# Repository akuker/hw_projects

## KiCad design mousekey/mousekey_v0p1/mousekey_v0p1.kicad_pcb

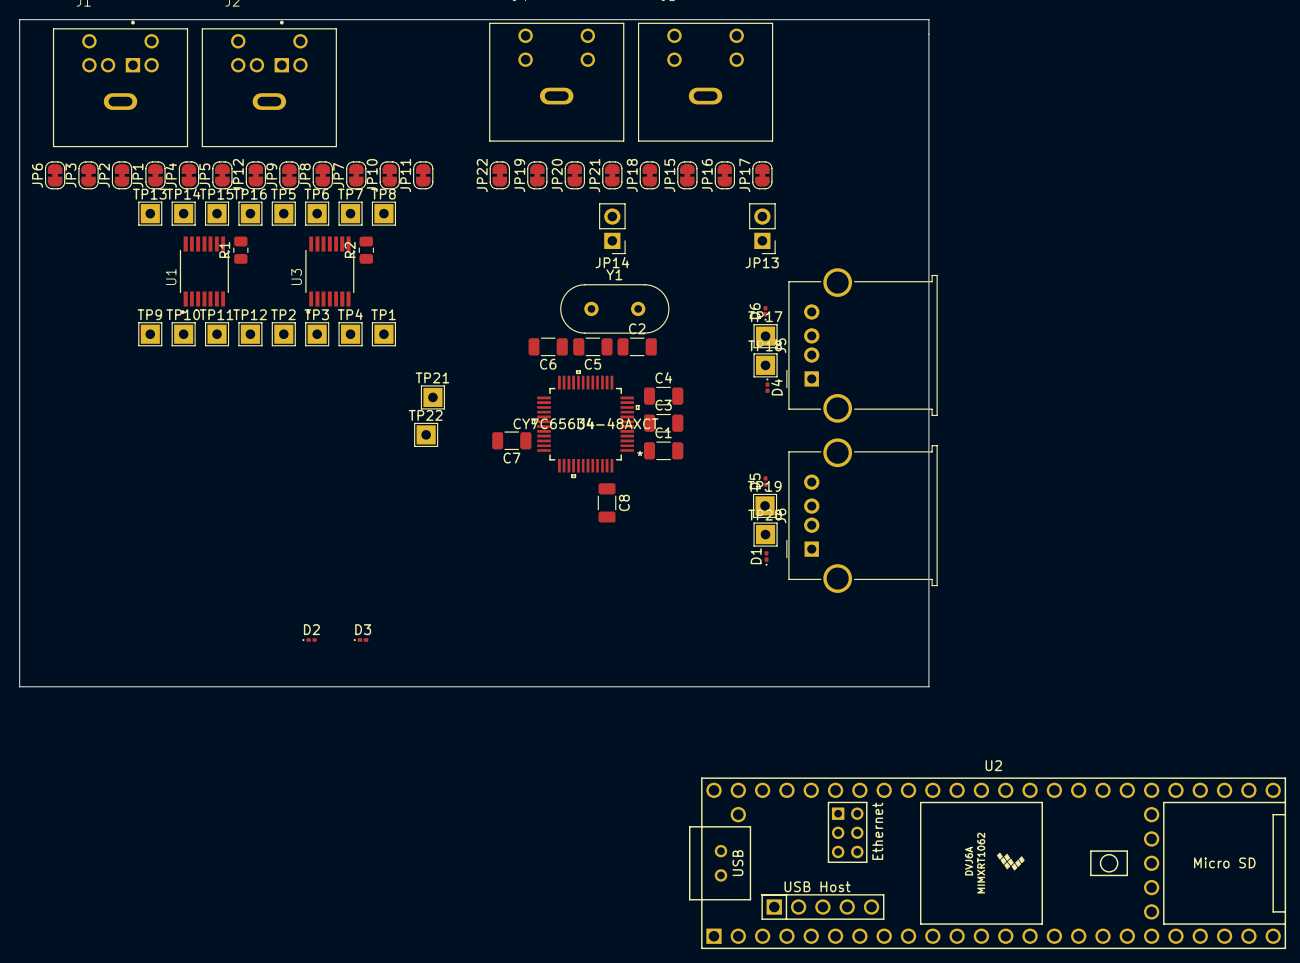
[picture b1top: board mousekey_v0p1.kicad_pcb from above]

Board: 2 copper layers, 95.0 x 69.7 mm, 71 parts (0 on the bottom side), 54 nets, no tracks yet.

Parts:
C1, C3, C4, C6, C7, C8: 0.1u; C_1206_3216Metric
C2, C5: 20p; C_1206_3216Metric
D1, D2, D3, D4, D5, D6: PGB1010603MR; D_0201_0603Metric
J1, J2: MD-60S; CUI_MD-60S
J3, J4: MD-40S; CUI_MD-40S
J5, J6: USB_A; USB_A_Molex_67643_Horizontal
JP1, JP2, JP3, JP4, JP5, JP6, JP7, JP8, JP9, JP10, JP11, JP12, JP15, JP16, JP17, JP18, JP19, JP20, JP21, JP22: SolderJumper_2_Bridged; SolderJumper-2_P1.3mm_Bridged_RoundedPad1.0x1.5mm
JP13, JP14: Jumper_2_Bridged; PinHeader_1x02_P2.54mm_Vertical
R1, R2: 0 ohm; R_0805_2012Metric
TP1, TP2, TP3, TP4, TP5, TP6, TP7, TP8, TP9, TP10, TP11, TP12, TP13, TP14, TP15, TP16, TP17, TP18, TP19, TP20, TP21, TP22: TestPoint; TestPoint_THTPad_2.0x2.0mm_Drill1.0mm
U1, U3: LSF0204DPWR; SOP65P640X120-14N
U2: Teensy4.1; Teensy41
U4: CY7C65634-48AXCT
Y1: 12MHz; Crystal_HC49-U_Vertical

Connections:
+3V3: U1.1 (VREF_A), U3.1 (VREF_A)
+5V: C8.1, J5.1 (VBUS), J6.1 (VBUS), JP3.1 (A), JP13.1 (A), JP14.1 (A), U1.14 (VREF_B), U3.14 (VREF_B), U4.47 (VCC)
ADB_A_Data: JP15.1 (A), TP5.1, U3.13 (B1)
ADB_A_PWR: JP16.1 (A), TP6.1, U3.12 (B2)
ADB_B_Data: JP19.1 (A), TP7.1, U3.11 (B3)
ADB_B_PWR: JP20.1 (A), TP8.1, U3.10 (B4)
GND: C1.2, C2.2, C3.2, C4.2, C5.2, C7.2, C8.2, J1.S1 (SHIELD), J2.S1 (SHIELD), J3.S1 (SHIELD), J4.S1 (SHIELD), J5.4 (GND), J6.4 (GND), JP4.1 (A), JP10.1 (A), JP18.1 (A), JP22.1 (A), R1.1, R2.1, U1.7 (GND), U3.7 (GND), U4.2 (GND), U4.8 (GND), U4.13 (GND), U4.20 (GND)
GNDPWR: D1.2 (A2), D2.2 (A2), D3.2 (A2), D4.2 (A2), D5.2 (A2), D6.2 (A2), J5.5 (Shield), J6.5 (Shield)
unnamed: J1.1, JP1.2 (B)
unnamed: J1.2, JP2.2 (B)
unnamed: J1.3, JP3.2 (B)
unnamed: J1.5, JP4.2 (B)
unnamed: J1.6, JP5.2 (B)
unnamed: J1.8, JP6.2 (B)
unnamed: J2.1, JP7.2 (B)
unnamed: J2.2, JP8.2 (B)
unnamed: J2.3, JP9.2 (B)
unnamed: J2.5, JP10.2 (B)
unnamed: J2.6, JP11.2 (B)
unnamed: J2.8, JP12.2 (B)
unnamed: J3.3, JP15.2 (B)
unnamed: J3.5, JP16.2 (B)
unnamed: J3.6, JP17.2 (B)
unnamed: J3.8, JP18.2 (B)
unnamed: J4.3, JP19.2 (B)
unnamed: J4.5, JP20.2 (B)
unnamed: J4.6, JP21.2 (B)
unnamed: J4.8, JP22.2 (B)
unnamed: JP13.2 (B), JP17.1 (A)
unnamed: JP14.2 (B), JP21.1 (A)
unnamed: R1.2, U1.8 (~EN)
unnamed: R2.2, U3.8 (~EN)
PS2_A_CLK: JP5.1 (A), TP14.1, U1.12 (B2)
PS2_A_Data: JP1.1 (A), TP13.1, U1.13 (B1)
PS2_B_CLK: JP11.1 (A), TP16.1, U1.10 (B4)
PS2_B_Data: JP7.1 (A), TP15.1, U1.11 (B3)
TTL_ADB_A_Data: TP1.1, U3.2 (A1)
TTL_ADB_A_PWR: TP2.1, U3.3 (A2)
TTL_ADB_B_Data: TP3.1, U3.4 (A3)
TTL_ADB_B_PWR: TP4.1, U3.5 (A4)
TTL_PS2_A_CLK: TP10.1, U1.3 (A2)
TTL_PS2_A_Data: TP9.1, U1.2 (A1)
TTL_PS2_B_CLK: TP12.1, U1.5 (A4)
TTL_PS2_B_Data: TP11.1, U1.4 (A3)
USB_DD1_N: D1.1 (A1), J6.2 (D-), TP20.1, U4.5 (DD-1)
USB_DD1_P: D5.1 (A1), J6.3 (D+), TP19.1, U4.6 (DD+1)
USB_DD2_N: D4.1 (A1), J5.2 (D-), TP18.1, U4.9 (DD-2)
USB_DD2_P: D6.1 (A1), J5.3 (D+), TP17.1, U4.10 (DD+2)
USB_DIN_N: D3.1 (A1), TP22.1, U4.3 (D-)
USB_DIN_P: D2.1 (A1), TP21.1, U4.4 (D+)
USB_VCC_A: C1.1, C3.1, C4.1, C6.1, U4.1 (VCC_A), U4.7 (VCC_A), U4.12 (VCC_A), U4.16 (VCC_A)
USB_VCC_D: C7.1, U4.34 (VCC_D)
USB_XIN: C2.1, U4.14 (XIN), Y1.1
USB_XOUT: C5.1, U4.15 (XOUT), Y1.2

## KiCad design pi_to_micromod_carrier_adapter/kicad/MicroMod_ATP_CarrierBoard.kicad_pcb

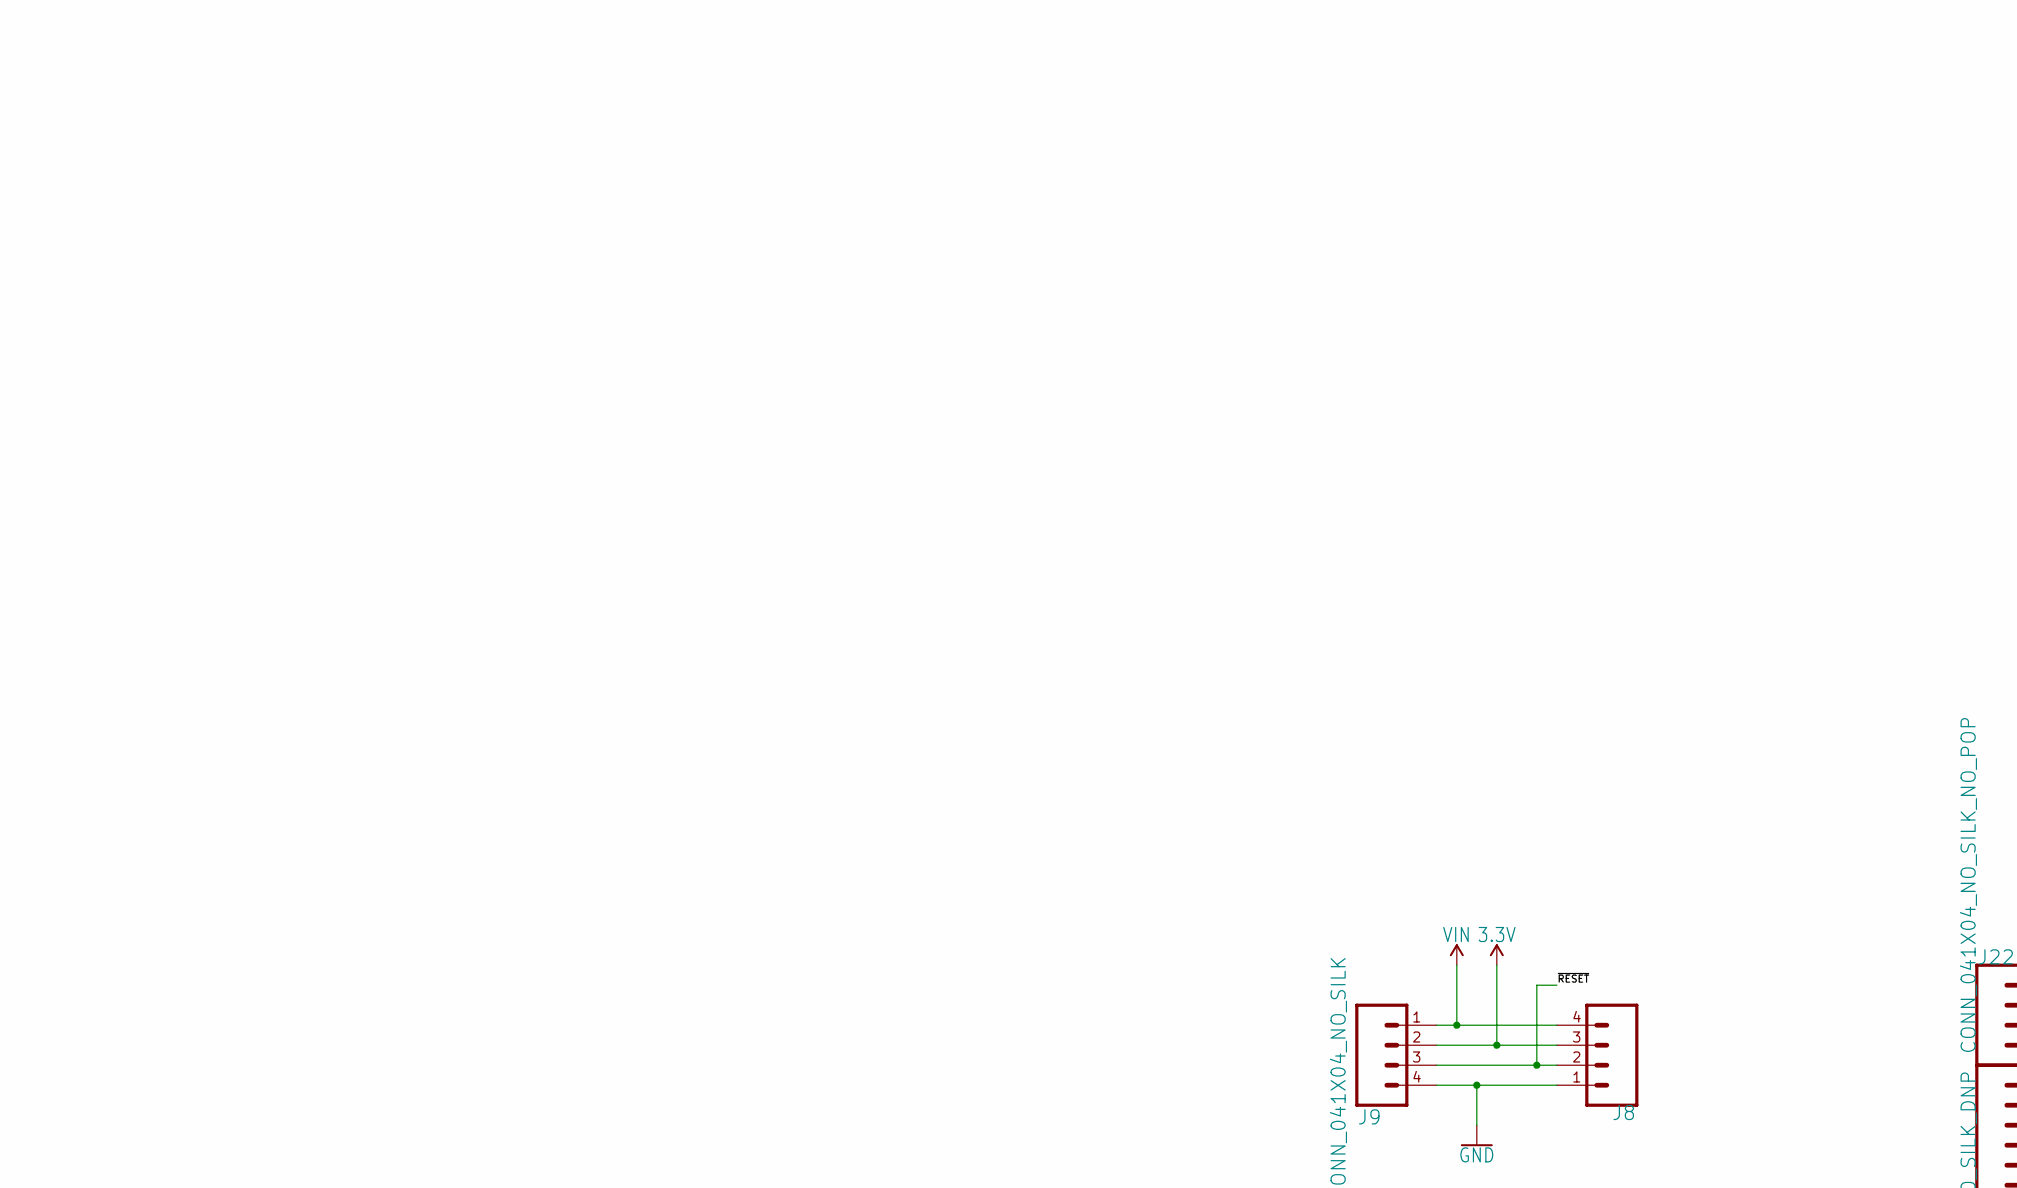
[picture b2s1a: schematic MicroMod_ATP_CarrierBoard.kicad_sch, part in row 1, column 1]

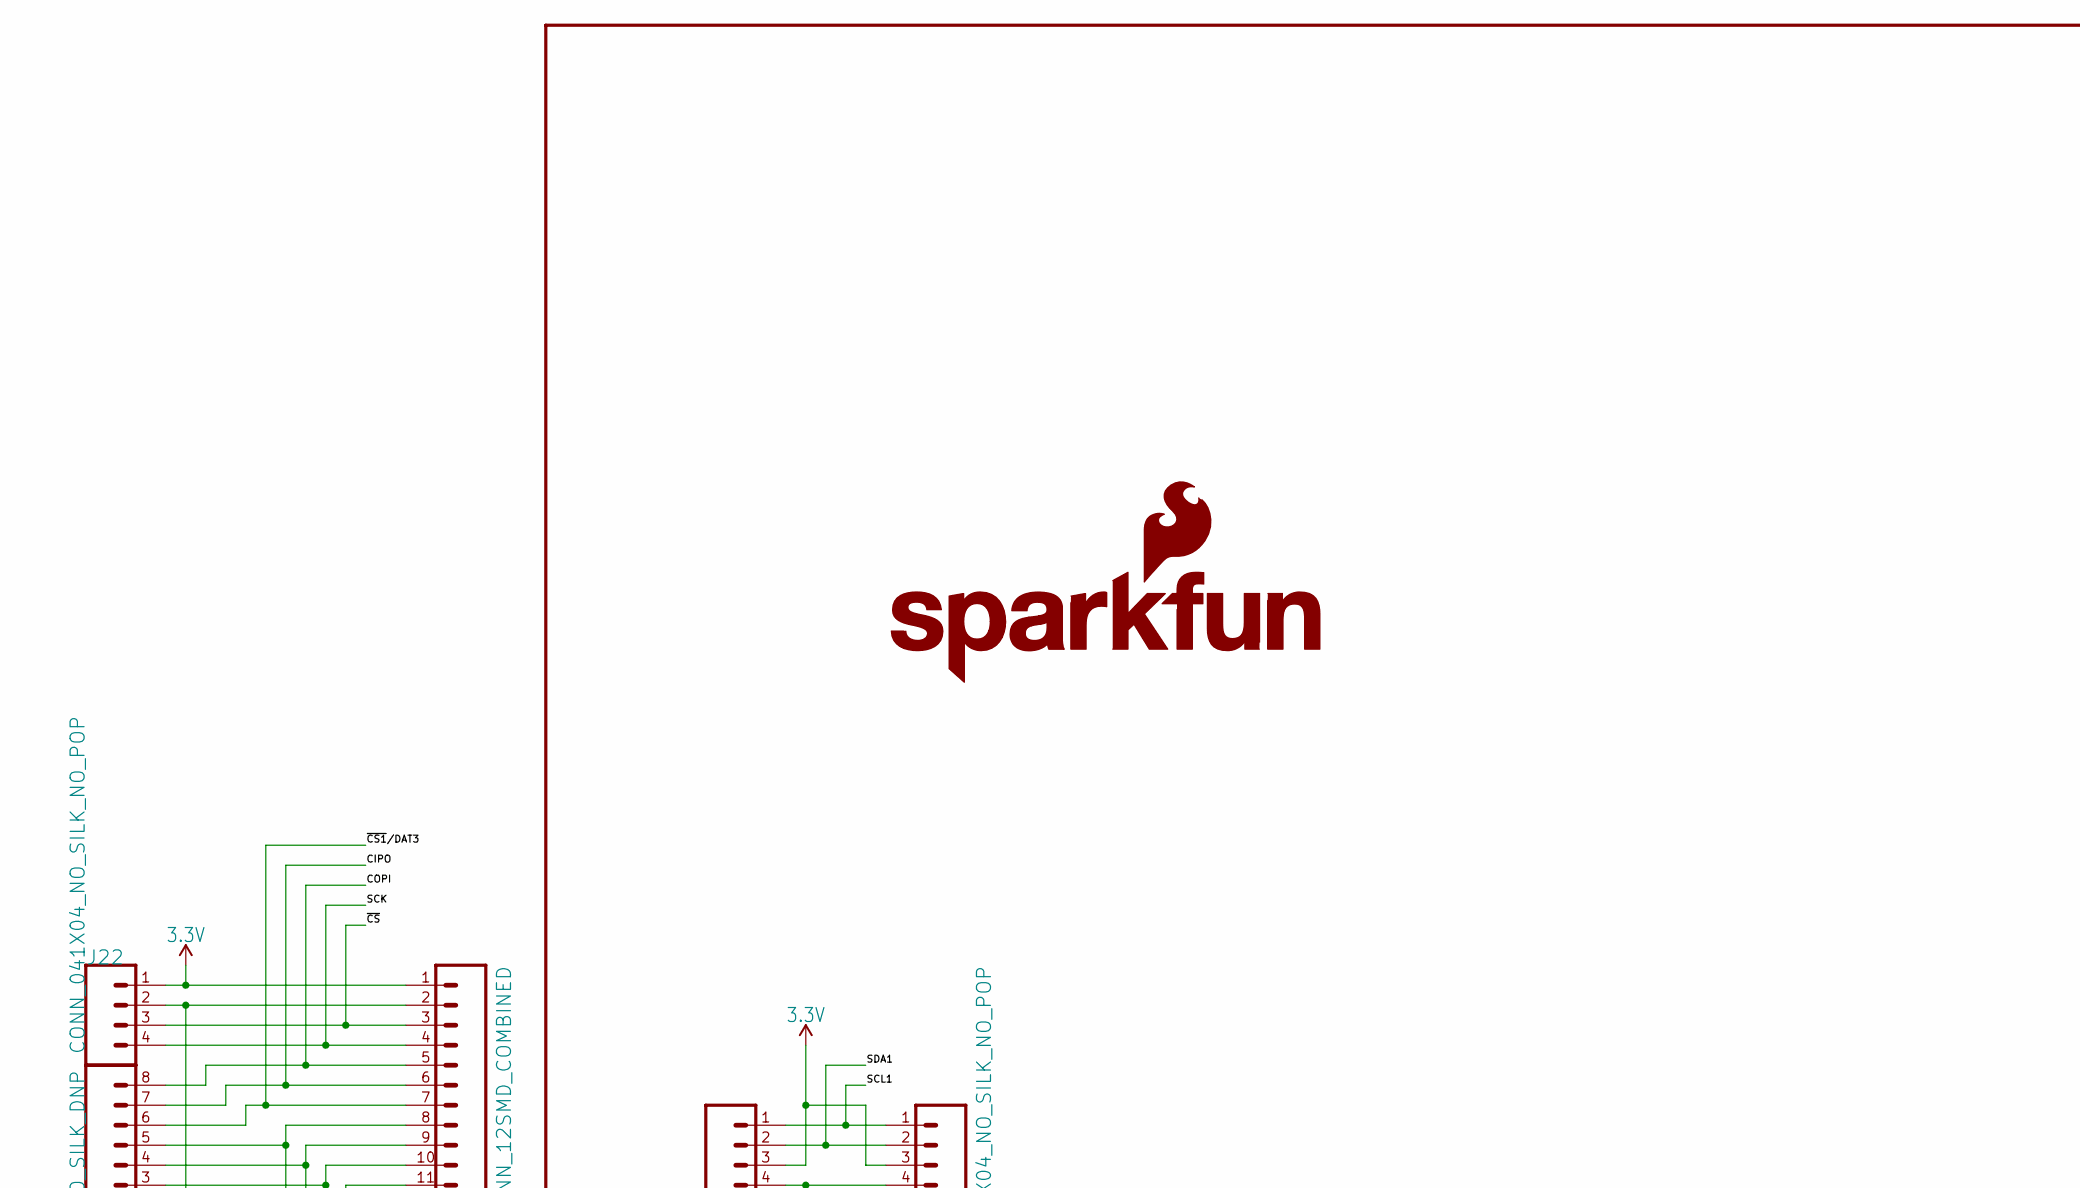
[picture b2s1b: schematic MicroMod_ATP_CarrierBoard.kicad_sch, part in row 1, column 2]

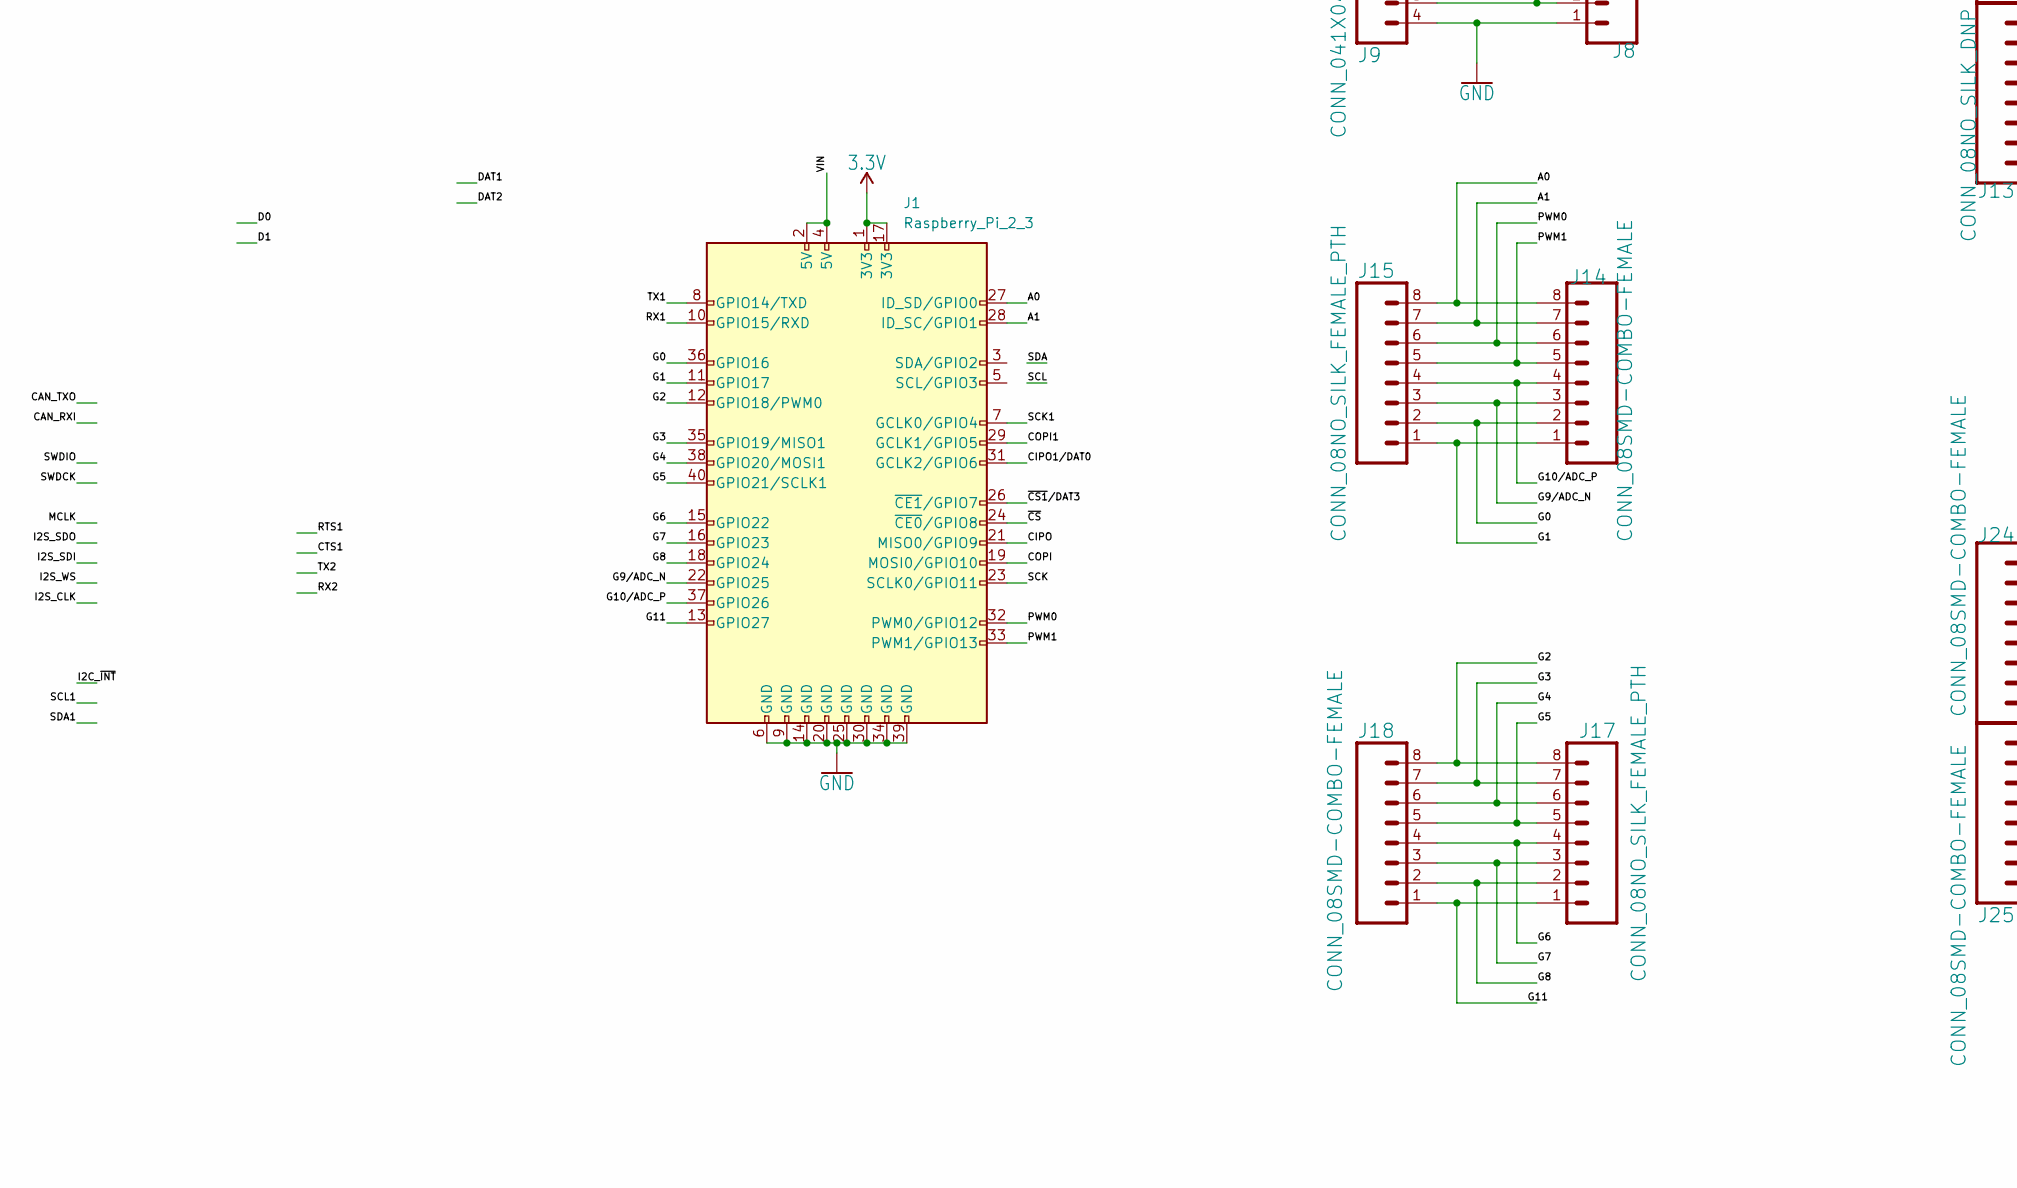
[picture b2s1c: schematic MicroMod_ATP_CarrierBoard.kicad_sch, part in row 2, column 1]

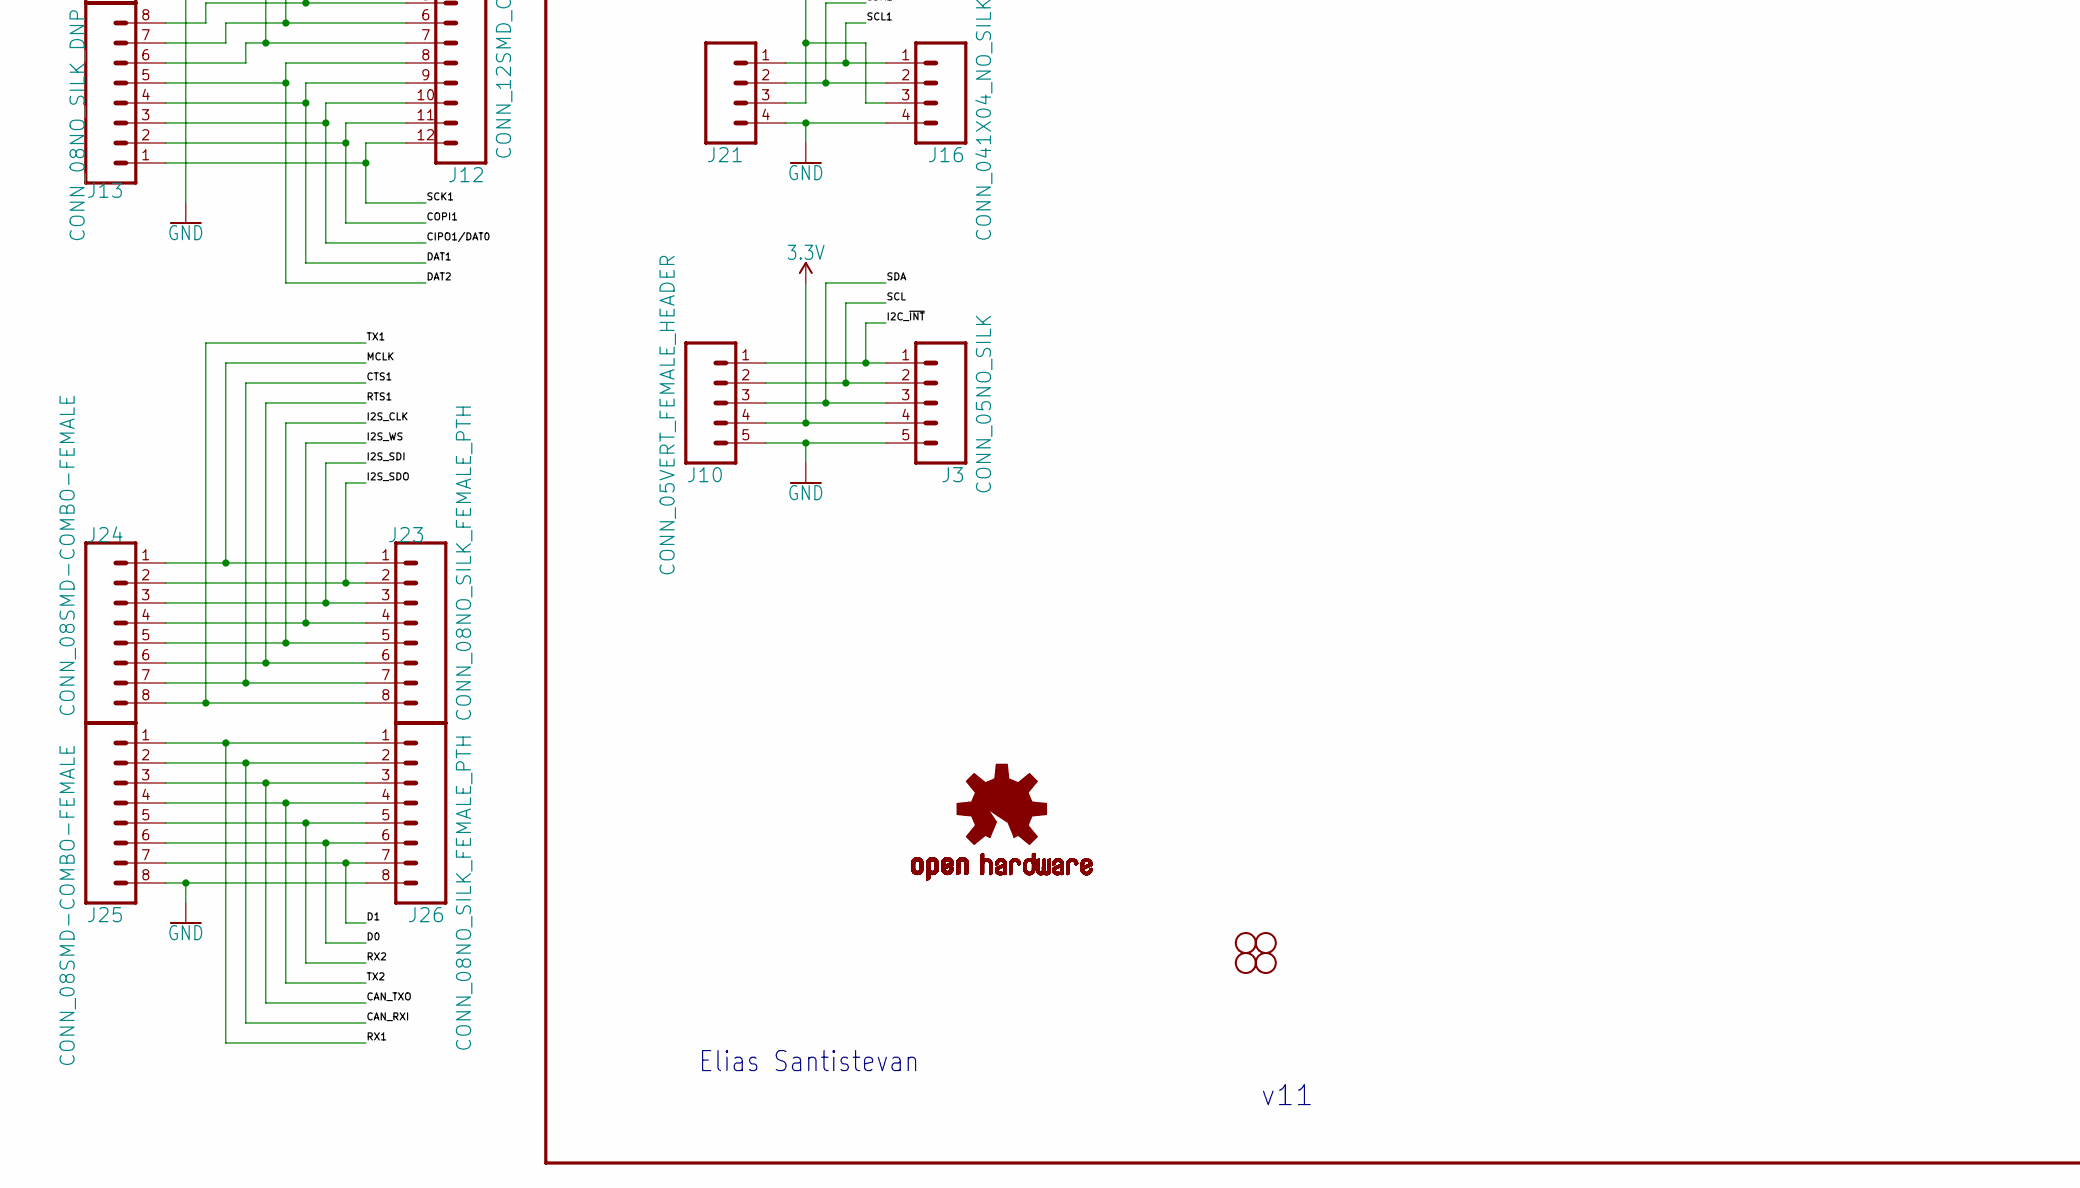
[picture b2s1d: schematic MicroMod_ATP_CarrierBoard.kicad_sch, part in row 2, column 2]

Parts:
FRAME1: FRAME-LEDGER; CREATIVE_COMMONS
H1, H2, H3, H4: STAND-OFF
J1: Raspberry_Pi_2_3; PinHeader_2x20_P2.54mm_Vertical
J3: CONN_05NO_SILK; 1X05_NO_SILK
J8, J21: 1X04_SMD_STRAIGHT_COMBO; PinHeader_1x04_P2.54mm_Vertical
J9: CONN_041X04_NO_SILK; 1X04_NO_SILK
J10: CONN_05VERT_FEMALE_HEADER; PinHeader_1x05_P2.54mm_Vertical
J12: CONN_12SMD_COMBINED; PinHeader_1x12_P2.54mm_Vertical
J13: CONN_08NO_SILK_DNP; 1X08_NO_SILK
J14, J17, J24, J25: CONN_08SMD-COMBO-FEMALE; PinHeader_1x08_P2.54mm_Vertical
J15, J23, J26: CONN_08NO_SILK_FEMALE_PTH; 1X08_NO_SILK
J16, J22: CONN_041X04_NO_SILK_NO_POP; 1X04_NO_SILK
J18: CONN_08NO_SILK_FEMALE_PTH; PinHeader_1x08_P2.54mm_Vertical
LOGO1: SFE_LOGO_NAME_FLAME.1_INCH; SFE_LOGO_NAME_FLAME_.1
LOGO3: OSHW-LOGOMINI; OSHW-LOGO-MINI

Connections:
3.3V: J1.1 (3V3), J1.17 (3V3), J3.4, J8.3, J9.2, J10.4, J12.1, J16.3, J21.3, J22.1
/A0: J1.27 (ID_SD/GPIO0), J14.8, J15.8
/A1: J1.28 (ID_SC/GPIO1), J14.7, J15.7
/CAN_RXI: J25.2, J26.2
/CAN_TXO: J25.3, J26.3
/CIPO: J1.21 (MISO0/GPIO9), J12.6, J13.7
/CIPO1/DAT0: J1.31 (GCLK2/GPIO6), J12.10, J13.3
/COPI: J1.19 (MOSI0/GPIO10), J12.5, J13.8
/COPI1: J1.29 (GCLK1/GPIO5), J12.11, J13.2
/CTS1: J23.7, J24.7
/D0: J25.6, J26.6
/D1: J25.7, J26.7
/DAT1: J12.9, J13.4
/DAT2: J12.8, J13.5
/G0: J1.36 (GPIO16), J14.2, J15.2
/G1: J1.11 (GPIO17), J14.1, J15.1
/G2: J1.12 (GPIO18/PWM0), J17.8, J18.8
/G3: J1.35 (GPIO19/MISO1), J17.7, J18.7
/G4: J1.38 (GPIO20/MOSI1), J17.6, J18.6
/G5: J1.40 (GPIO21/SCLK1), J17.5, J18.5
/G6: J1.15 (GPIO22), J17.4, J18.4
/G7: J1.16 (GPIO23), J17.3, J18.3
/G8: J1.18 (GPIO24), J17.2, J18.2
/G9/ADC_N: J1.22 (GPIO25), J14.3, J15.3
/G10/ADC_P: J1.37 (GPIO26), J14.4, J15.4
/G11: J1.13 (GPIO27), J17.1, J18.1
/I2C_~INT: J3.1, J10.1
/I2S_CLK: J23.5, J24.5
/I2S_SDI: J23.3, J24.3
/I2S_SDO: J23.2, J24.2
/I2S_WS: J23.4, J24.4
/MCLK: J23.1, J24.1
/PWM0: J1.32 (PWM0/GPIO12), J14.6, J15.6
/PWM1: J1.33 (PWM1/GPIO13), J14.5, J15.5
/RTS1: J23.6, J24.6
/RX1: J1.10 (GPIO15/RXD), J25.1, J26.1
/RX2: J25.5, J26.5
/SCK: J1.23 (SCLK0/GPIO11), J12.4, J22.4
/SCK1: J1.7 (GCLK0/GPIO4), J12.12, J13.1
/SCL: J3.2, J10.2
/SCL1: J16.1, J21.1
/SDA: J3.3, J10.3
/SDA1: J16.2, J21.2
/TX1: J1.8 (GPIO14/TXD), J23.8, J24.8
/TX2: J25.4, J26.4
/~CS1/DAT3: J1.26 (~CE1/GPIO7), J12.7, J13.6
/~CS: J1.24 (~CE0/GPIO8), J12.3, J22.3
/~RESET: J8.2, J9.3
GND: J1.6 (GND), J1.9 (GND), J1.14 (GND), J1.20 (GND), J1.25 (GND), J1.30 (GND), J1.34 (GND), J1.39 (GND), J3.5, J8.1, J9.4, J10.5, J12.2, J16.4, J21.4, J22.2, J25.8, J26.8
VIN: J1.2 (5V), J1.4 (5V), J8.4, J9.1

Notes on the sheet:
Elias Santistevan
v11

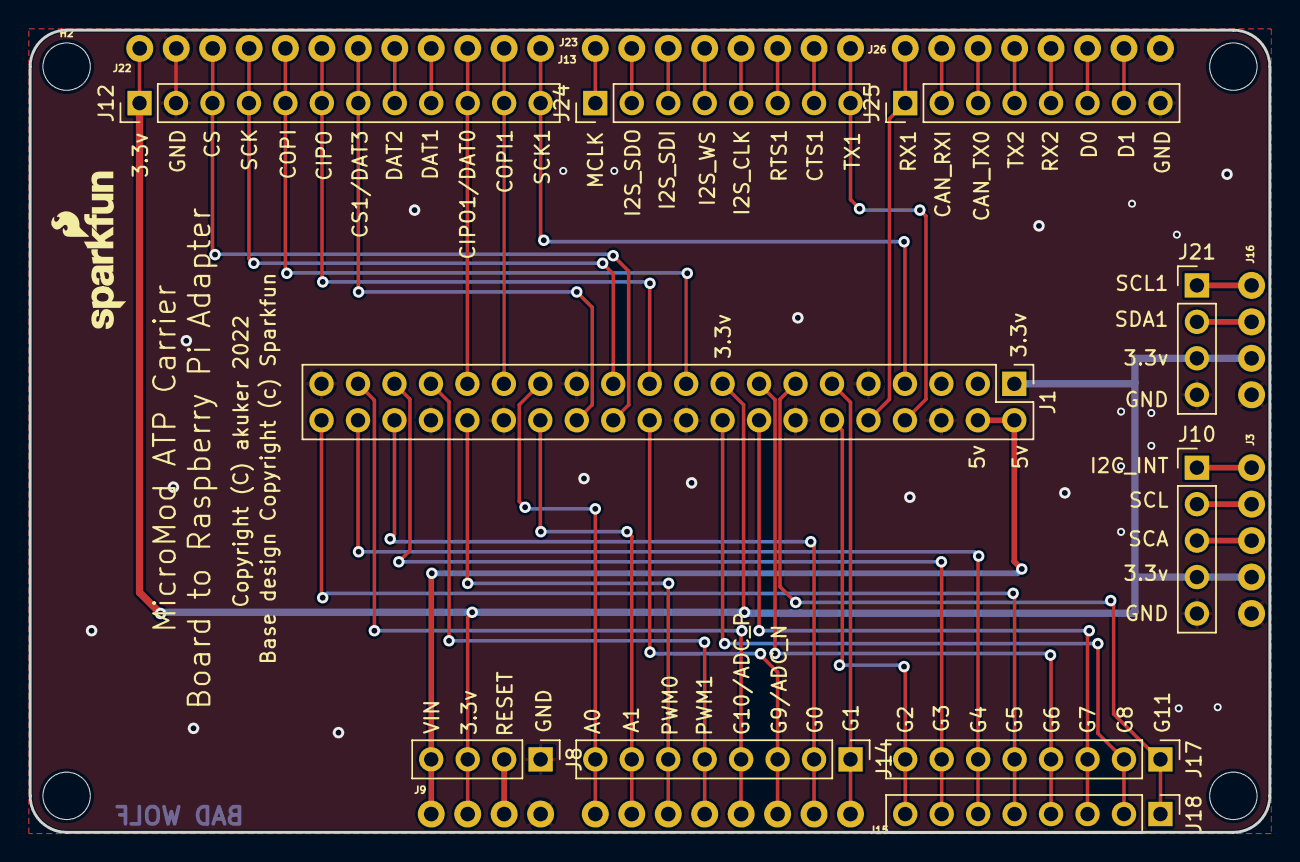
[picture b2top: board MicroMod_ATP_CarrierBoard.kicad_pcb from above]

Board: 2 copper layers, 86.4 x 55.9 mm, 25 parts (1 on the bottom side), 50 nets.

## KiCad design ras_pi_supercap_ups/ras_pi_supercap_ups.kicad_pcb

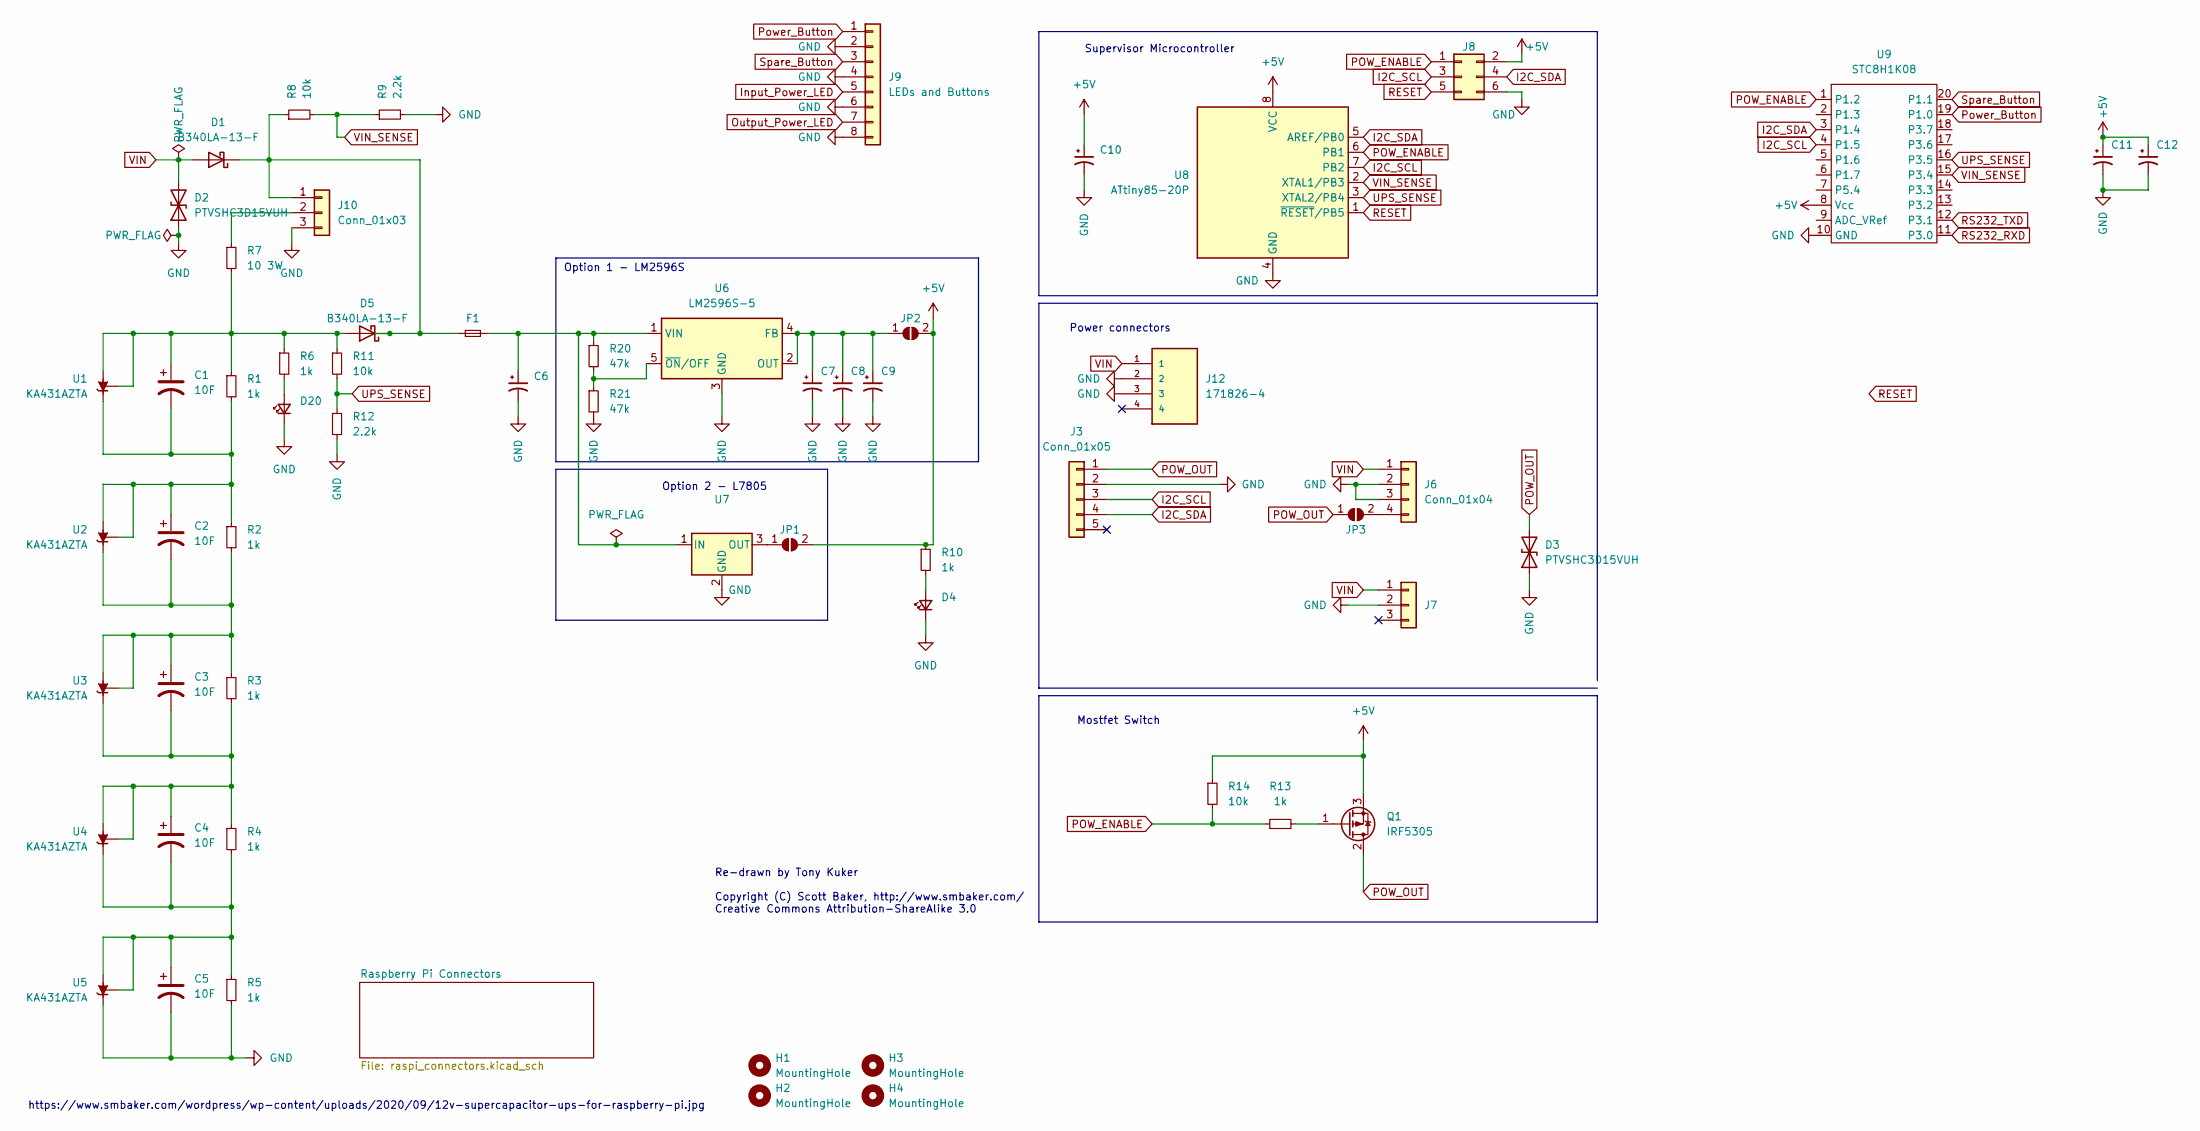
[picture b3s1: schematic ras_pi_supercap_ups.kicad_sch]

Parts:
C1, C2, C3, C4, C5: 10F; CP_Radial_D12.5mm_P5.00mm; DigikeyPN 478-10996-ND
C6: 10u 25V X7R; C_0805_2012Metric; DigikeyPN 445-FK26X7R1E106K-ND
C7, C8, C9, C10, C11: 22u 10V X7R; C_0805_2012Metric; DigikeyPN 445-173294-1-ND
C12: 0.1u; C_0805_2012Metric; LCSC C28233
D1, D5: B340LA-13-F; D_SMA; LCSC C17101
D2, D3: PTVSHC3D15VUH; D_SOD-323; LCSC C312234
D4, D20: Green; LED_0805_2012Metric; LCSC C2293
F1: Fuse_Small; Fuse_1206_3216Metric; LCSC C140540
H1, H2, H3, H4: MountingHole; MountingHole_2.7mm_M2.5
J3: Conn_01x05; PinHeader_1x05_P2.54mm_Vertical; DigikeyPN NA
J6: Conn_01x04; PinHeader_1x04_P2.54mm_Vertical; DigikeyPN A106204-ND
J7: DigikeyPN A106204-ND
J8: Conn_02x03_Odd_Even; PinHeader_2x03_P2.54mm_Vertical; DigikeyPN NA
J9: LEDs and Buttons; PinHeader_1x08_P2.54mm_Vertical
J10: Conn_01x03; PinHeader_1x03_P2.54mm_Vertical; DigikeyPN NA
J12: 171826-4; TE_171826-4
JP1, JP2, JP3: SolderJumper_2_Open; SolderJumper-2_P1.3mm_Open_RoundedPad1.0x1.5mm; DigikeyPN NA
Q1: IRF5305; TO-263-2; LCSC C878890
R1, R2, R3, R4, R5: 1k; R_1206_3216Metric; DigikeyPN CF14JT1K00CT-ND
R6, R10, R13: 1k; R_0805_2012Metric; DigikeyPN CF14JT1K00CT-ND
R7: 10 3W; R_Axial_DIN0516_L15.5mm_D5.0mm_P25.40mm_Horizontal; DigikeyPN YAG1228CT-ND
R8, R11, R14: 10k; R_0805_2012Metric; DigikeyPN CF14JT10K0CT-ND
R9, R12: 2.2k; R_0805_2012Metric; DigikeyPN CF14JT2K20TR-ND
R20, R21: 47k; R_0805_2012Metric; DigikeyPN CF14JT47K0TR-ND
U1, U2, U3, U4, U5: KA431AZTA; TO-92_Inline; LCSC C124501
U6: LM2596S-5; TO-263-5_TabPin3; DigikeyPN LM2596S-5.0-ND
U7: DigikeyPN 497-1443-5-ND
U8: ATtiny85-20P; DIP-8_W7.62mm; DigikeyPN ATTINY85-20PU-ND
U9: STC8H1K08; TSSOP-20_4.4x5mm_P0.5mm; LCSC C915673

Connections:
+5V: C10.1, C11.1, C12.1, J8.2, JP1.2 (B), JP2.2 (B), Q1.3 (S), R10.1, R14.1, U8.8 (VCC), U9.8 (Vcc)
GND: C5.2, C6.2, C7.2, C8.2, C9.2, C10.2, C11.2, C12.2, D2.1 (A1), D3.1 (A1), D4.1 (K), D20.1 (K), J3.2, J6.2, J6.3, J7.2, J8.6, J9.2, J9.4, J9.6, J9.8, J10.3, J12.2, J12.3, R5.2, R9.2, R12.2, R21.2, U5.3 (K), U6.3 (GND), U7.2 (GND), U8.4 (GND), U9.10 (GND); also elsewhere on the board
I2C_SCL: J3.3, J8.3, U8.7 (PB2), U9.4 (P1.5); also elsewhere on the board
I2C_SDA: J3.4, J8.4, U8.5 (AREF/PB0), U9.3 (P1.4); also elsewhere on the board
Input_Power_LED: J9.5
unnamed: C1.1, D5.2 (A), R1.1, R6.1, R7.2, R11.1, U1.1 (REF), U1.2 (A)
unnamed: C1.2, C2.1, R1.2, R2.1, U1.3 (K), U2.1 (REF), U2.2 (A)
unnamed: C2.2, C3.1, R2.2, R3.1, U2.3 (K), U3.1 (REF), U3.2 (A)
unnamed: C3.2, C4.1, R3.2, R4.1, U3.3 (K), U4.1 (REF), U4.2 (A)
unnamed: C4.2, C5.1, R4.2, R5.1, U4.3 (K), U5.1 (REF), U5.2 (A)
unnamed: C6.1, F1.2, R20.1, U6.1 (VIN), U7.1 (IN)
unnamed: C7.1, C8.1, C9.1, JP2.1 (A), U6.2 (OUT), U6.4 (FB)
unnamed: D1.1 (K), D5.1 (K), F1.1, J10.1, R8.1
unnamed: D4.2 (A), R10.2
unnamed: D20.2 (A), R6.2
unnamed: J6.4, JP3.2 (B)
unnamed: J10.2, R7.1
unnamed: JP1.1 (A), U7.3 (OUT)
unnamed: Q1.1 (G), R13.2
unnamed: R20.2, R21.1, U6.5 (~ON/OFF)
Output_Power_LED: J9.7
POW_ENABLE: J8.1, R13.1, R14.2, U8.6 (PB1), U9.1 (P1.2)
POW_OUT: D3.2 (A2), J3.1, JP3.1 (A), Q1.2 (D); also elsewhere on the board
Power_Button: J9.1, U9.19 (P1.0)
RESET: J8.5, U8.1 (~RESET/PB5)
RS232_RXD: U9.11 (P3.0)
RS232_TXD: U9.12 (P3.1)
Spare_Button: J9.3, U9.20 (P1.1)
UPS_SENSE: R11.2, R12.1, U8.3 (XTAL2/PB4), U9.16 (P3.5)
VIN: D1.2 (A), D2.2 (A2), J6.1, J7.1, J12.1
VIN_SENSE: R8.2, R9.1, U8.2 (XTAL1/PB3), U9.15 (P3.4)

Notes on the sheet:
Mostfet Switch
https://www.smbaker.com/wordpress/wp-content/uploads/2020/09/12v-supercapacitor-ups-for-raspberry-pi.jpg
Power connectors
Option 2 - L7805
Re-drawn by Tony Kuker Copyright (C) Scott Baker, http://www.smbaker.com/ Creative Commons Attribution-ShareAlike 3.0
Option 1 - LM2596S
Supervisor Microcontroller

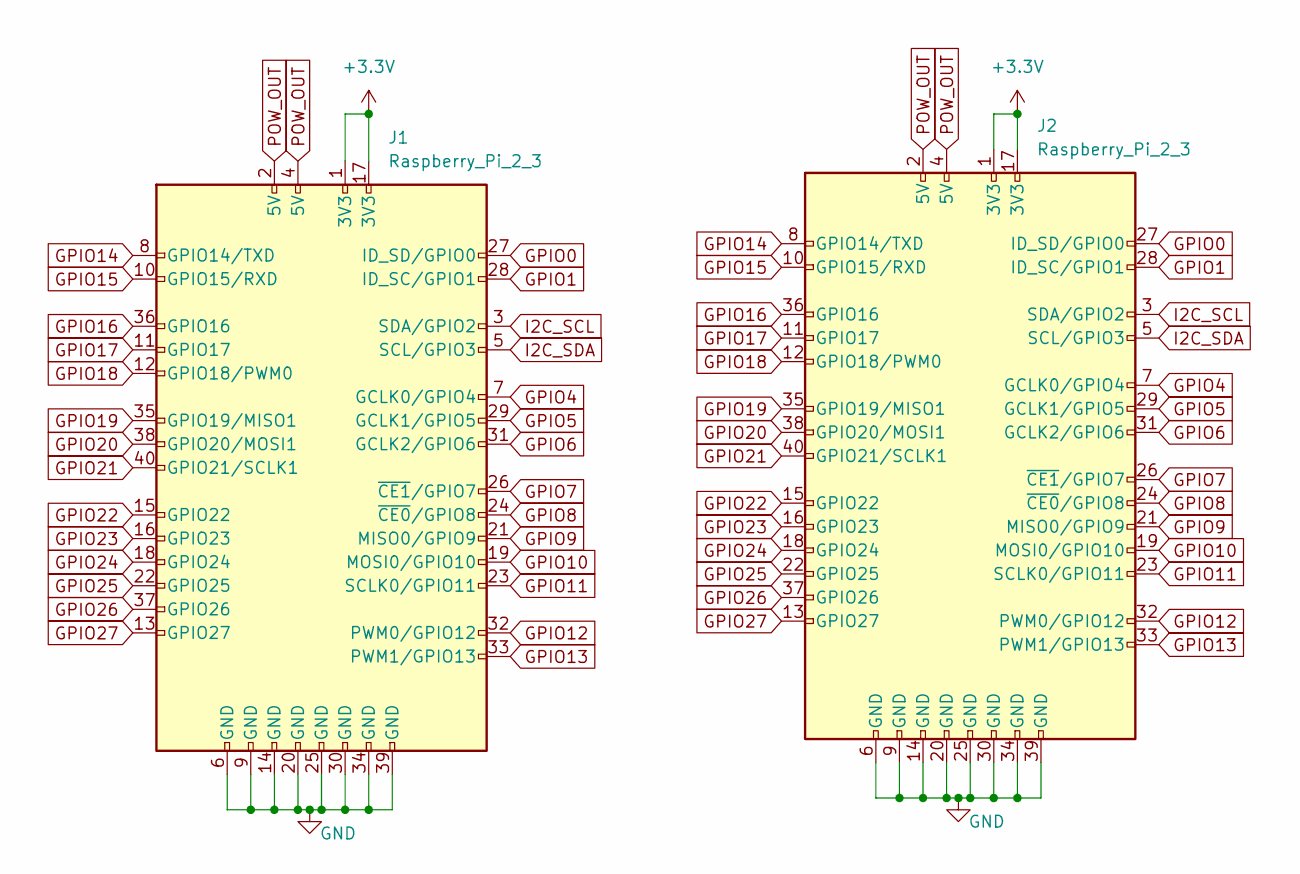
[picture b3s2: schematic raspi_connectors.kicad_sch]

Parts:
J1, J2: Raspberry_Pi_2_3

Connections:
+3V3: J1.1 (3V3), J1.17 (3V3), J2.1 (3V3), J2.17 (3V3)
GND: J1.6 (GND), J1.9 (GND), J1.14 (GND), J1.20 (GND), J1.25 (GND), J1.30 (GND), J1.34 (GND), J1.39 (GND), J2.6 (GND), J2.9 (GND), J2.14 (GND), J2.20 (GND), J2.25 (GND), J2.30 (GND), J2.34 (GND), J2.39 (GND); also elsewhere on the board
GPIO0: J1.27 (ID_SD/GPIO0), J2.27 (ID_SD/GPIO0)
GPIO1: J1.28 (ID_SC/GPIO1), J2.28 (ID_SC/GPIO1)
GPIO4: J1.7 (GCLK0/GPIO4), J2.7 (GCLK0/GPIO4)
GPIO5: J1.29 (GCLK1/GPIO5), J2.29 (GCLK1/GPIO5)
GPIO6: J1.31 (GCLK2/GPIO6), J2.31 (GCLK2/GPIO6)
GPIO7: J1.26 (~CE1/GPIO7), J2.26 (~CE1/GPIO7)
GPIO8: J1.24 (~CE0/GPIO8), J2.24 (~CE0/GPIO8)
GPIO9: J1.21 (MISO0/GPIO9), J2.21 (MISO0/GPIO9)
GPIO10: J1.19 (MOSI0/GPIO10), J2.19 (MOSI0/GPIO10)
GPIO11: J1.23 (SCLK0/GPIO11), J2.23 (SCLK0/GPIO11)
GPIO12: J1.32 (PWM0/GPIO12), J2.32 (PWM0/GPIO12)
GPIO13: J1.33 (PWM1/GPIO13), J2.33 (PWM1/GPIO13)
GPIO14: J1.8 (GPIO14/TXD), J2.8 (GPIO14/TXD)
GPIO15: J1.10 (GPIO15/RXD), J2.10 (GPIO15/RXD)
GPIO16: J1.36 (GPIO16), J2.36 (GPIO16)
GPIO17: J1.11 (GPIO17), J2.11 (GPIO17)
GPIO18: J1.12 (GPIO18/PWM0), J2.12 (GPIO18/PWM0)
GPIO19: J1.35 (GPIO19/MISO1), J2.35 (GPIO19/MISO1)
GPIO20: J1.38 (GPIO20/MOSI1), J2.38 (GPIO20/MOSI1)
GPIO21: J1.40 (GPIO21/SCLK1), J2.40 (GPIO21/SCLK1)
GPIO22: J1.15 (GPIO22), J2.15 (GPIO22)
GPIO23: J1.16 (GPIO23), J2.16 (GPIO23)
GPIO24: J1.18 (GPIO24), J2.18 (GPIO24)
GPIO25: J1.22 (GPIO25), J2.22 (GPIO25)
GPIO26: J1.37 (GPIO26), J2.37 (GPIO26)
GPIO27: J1.13 (GPIO27), J2.13 (GPIO27)
I2C_SCL: J1.3 (SDA/GPIO2), J2.3 (SDA/GPIO2); also elsewhere on the board
I2C_SDA: J1.5 (SCL/GPIO3), J2.5 (SCL/GPIO3); also elsewhere on the board
POW_OUT: J1.2 (5V), J1.4 (5V), J2.2 (5V), J2.4 (5V); also elsewhere on the board

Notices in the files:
pi_to_micromod_carrier_adapter/kicad/MicroMod_ATP_CarrierBoard.kicad_pcb:
Copyright (C) akuker 2022
Base design Copyright (c) Sparkfun
pi_to_micromod_carrier_adapter/kicad/MicroMod_ATP_CarrierBoard.kicad_sch:
https://creativecommons.org/licenses/by-sa/4.0
Released under the Creative Commons
rpi_led_board/rpi_led_board.kicad_pcb:
Copyright 2022 akuker
parts and their libraries:
Copyright 2016 Accelerated Designs. All rights reserved.
Released under the Creative Commons Attribution Share-Alike 4.0 License
